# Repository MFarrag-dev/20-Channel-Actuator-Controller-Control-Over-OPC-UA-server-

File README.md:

# 20-Channel-Actuator-Controller-Control-Over-OPC-UA-server-
20 Channel Actuator Controller

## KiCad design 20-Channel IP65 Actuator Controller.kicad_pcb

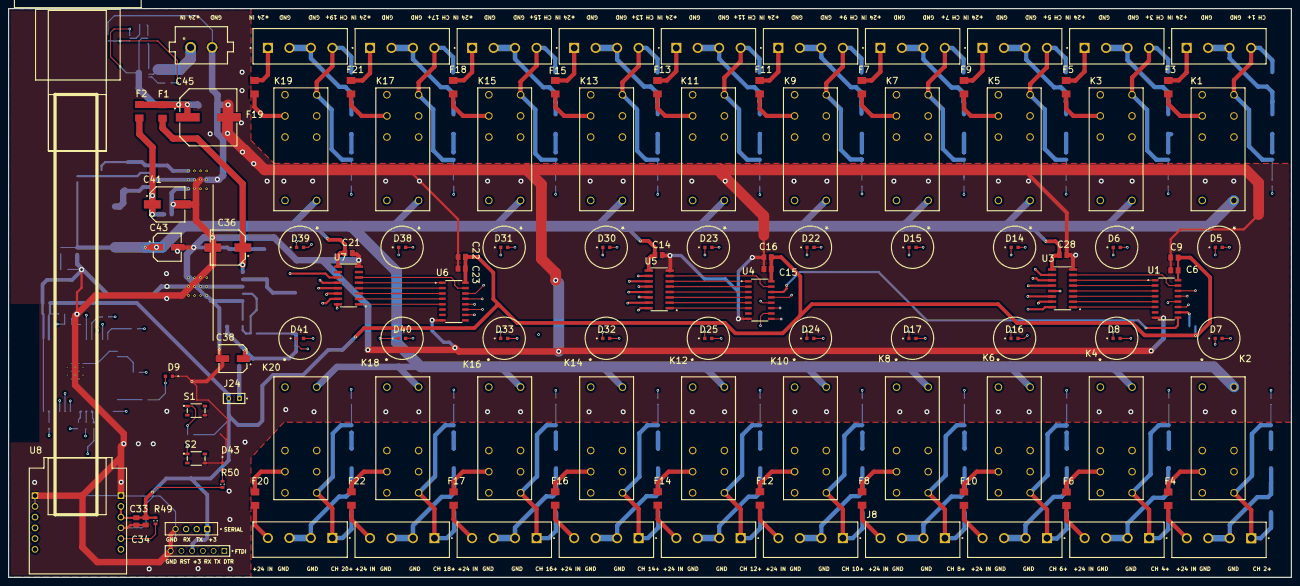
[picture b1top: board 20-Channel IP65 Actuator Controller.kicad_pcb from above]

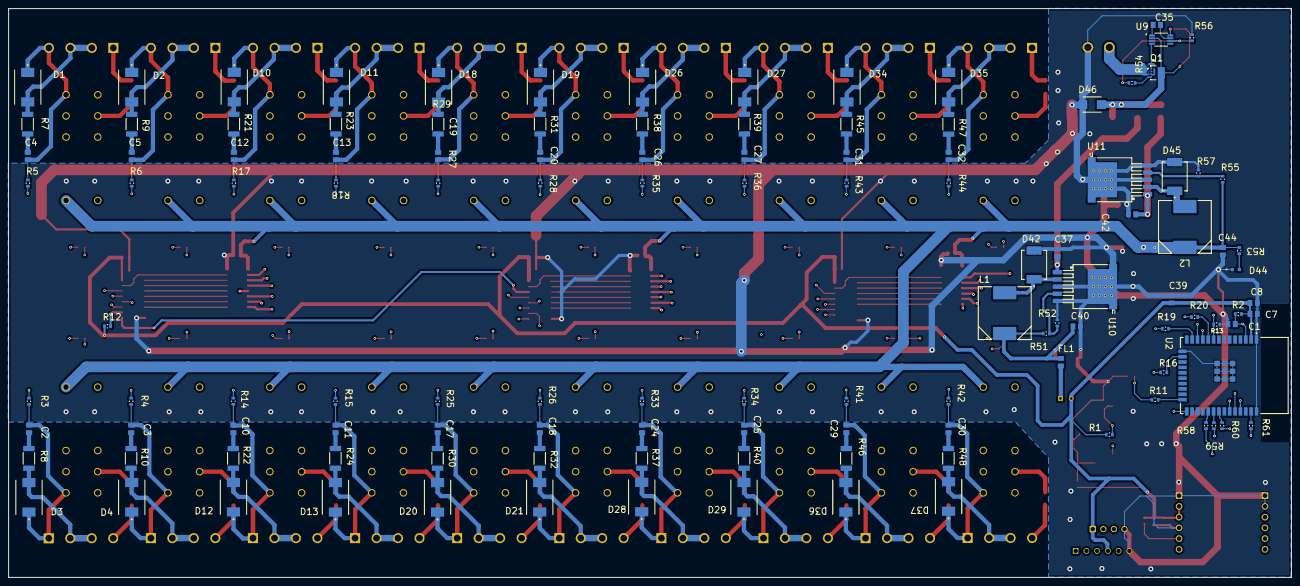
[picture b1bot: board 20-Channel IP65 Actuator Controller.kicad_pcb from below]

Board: 6 copper layers, 303.4 x 134.5 mm, 235 parts (120 on the bottom side), 205 nets.

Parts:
C1, C2, C3, C4, C5, C8, C9, C10, C11, C12, C13, C14, C16, C17, C18, C19, C20, C21, C23, C24, C25, C26, C27, C28, C29, C30, C31, C32, C34: 100nF; CAPC2012X88N
C6, C7, C15, C22, C33: 1uF; CAPC2012X88N
C35: 2.2uF; CAPC2012X88N
C36, C41: 100uF 50v; CAP_EEEHAH101UAP
C37, C42: 100nF 0805; CAPC2012X88N
C38, C43: 220uF 16v; CAP_EEEFTE221XAP
C39, C40, C44: 10uF 0805; CAPC2012X88N
C45: 470uF 50v; CAP_EEVTG1C471Q
D1, D2, D3, D4, D10, D11, D12, D13, D18, D19, D20, D21, D26, D27, D28, D29, D34, D35, D36, D37: SS54; SS54 DO-214AB SMC
D5, D6, D7, D8, D14, D15, D16, D17, D22, D23, D24, D25, D30, D31, D32, D33, D38, D39, D40, D41: Blue_LED; LED_0603
D9: LED_Green; LED_0603
D42, D45: SS34; DIO_SS34
D43: LED_Yellow; LED_0603
D44: LED_RED; LED_0603
D46: SMBJ28A; DIOM5436X244N
F1, F2: SF-1206SP550M-2; FUSC3115X66N
F3, F4, F5, F6, F7, F8, F9, F10, F11, F12, F13, F14, F15, F16, F17, F18, F19, F20, F21, F22: 0407002.WR; FUSC3115X66N
FL1: EMI Filter; BEADC2012X105N
J1, J2, J3, J4, J5, J6, J7, J8, J9, J10, J11, J12, J15, J16, J17, J18, J19, J20, J21, J22: 395316004; MOLEX_395316004
J13: HTSW-106-20-SM-S; SAMTEC_HTSW-106-20-SM-S
J14: B4B-XH-A(LF)(SN); JST_B4B-XH-A(LF)(SN)
J23: KF2EDGV-5.08-2P; 691305530002
J24: TD-101-X-A; SAMTEC_TD-101-X-A
K1, K2, K3, K4, K5, K6, K7, K8, K9, K10, K11, K12, K13, K14, K15, K16, K17, K18, K19, K20: G2RL-1-E DC5; RELAY_G2RL-1-E DC5_OMR
L1, L2: 33uH; INDM125125X600N
Q1: STL20N6F7; TRANS_STL3N65M2
R1, R2, R3, R4, R5, R6, R12, R13, R14, R15, R17, R18, R25, R26, R27, R28, R33, R34, R35, R36, R41, R42, R43, R44, R49: 10k; RES_ERJU03F1503V
R7, R8, R9, R10, R21, R22, R23, R24, R29, R30, R31, R32, R37, R38, R39, R40, R45, R46, R47, R48: 100R; RESC5025X65N
R11, R16, R19: 100R; RES_ERJU03F1503V
R20, R59, R60, R61: 22R; RES_ERJU03F1503V
R50: 470R; RES_ERJU03F1503V
R51: 3.2k; RES_ERJU03F1503V
R52, R57: 2k; RES_ERJU03F1503V
R53: 1k; RES_ERJU03F1503V
R54: 47R; RES_ERJU03F1503V
R55: 6.98k; RES_ERJU03F1503V
R56: 100k; RES_ERJU03F1503V
R58: 0R; RES_ERJU03F1503V
S1, S2: SKRPACE010; SW_SKRPACE010
U1, U4, U6: 74HC595D; SOP127P600X175-16N
U2: ESP32-WROOM-32; MODULE_ESP32-WROOM-32
U3, U5, U7: ULN2003AD; SOIC127P600X175-16N
U8: WIZ820IO; MODULE_WIZ820IO
U9: LM74610QDGKRQ1; SOP65P490X110-8N
U10, U11: LM2596S-ADJ/NOPB; KTT0005B

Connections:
+3.3: C6.1, C7.1, C8.1, C9.1, C15.1, C16.1, C22.1, C23.1, C33.1, C34.1, C39.2, J13.04, J14.1, J24.02, R1.2, R2.2, R12.1, R49.1, R50.2, U1.16, U2.2, U4.16, U6.16, U8.J2_2, U8.J2_3
+5.5: C14.1, C21.1, C28.1, C43.1, C44.1, K1.1, K2.8, K3.1, K4.8, K5.1, K6.8, K7.1, K8.8, K9.1, K10.8, K11.1, K12.8, K13.1, K14.8, K15.1, K16.8, K17.1, K18.8, K19.1, K20.8, L2.1, R53.2, R55.2, U3.9, U5.9, U7.9
+24: C45.1, D46.C, F1.1, F2.1, Q1.3, U9.2, U9.8
CH_1: K1.8, U3.10
CH_2: K2.1, U3.11
CH_3: K3.8, U3.12
CH_4: K4.1, U3.13
CH_5: K5.8, U3.14
CH_6: K6.1, U3.15
CH_7: K7.8, U3.16
CH_8: K8.1, U5.10
CH_9: K9.8, U5.11
CH_10: K10.1, U5.12
CH_11: K11.8, U5.13
CH_12: K12.1, U5.14
CH_13: K13.8, U5.15
CH_14: K14.1, U5.16
CH_15: K15.8, U7.16
CH_16: K16.1, U7.15
CH_17: K17.8, U7.14
CH_18: K18.1, U7.13
CH_19: K19.8, U7.12
CH_20: K20.1, U7.11
CLK: R19.1, U1.11, U4.11, U6.11
CLR: R12.2, U1.10, U2.11, U4.10, U6.10
DATA: R16.1, U1.14
DATA_2: U1.9, U4.14
DATA_3: U4.9, U6.14
DTR: J13.01, R1.1, S1.1, U2.25
EN: R13.2, U1.13, U2.9, U4.13, U6.13
FB_3.3: R51.1, R52.2, U10.4
FB_5.5: R55.1, R57.2, U11.4
GND: C1.1, C6.2, C7.2, C8.2, C9.2, C14.2, C15.2, C16.2, C21.2, C22.2, C23.2, C28.2, C33.2, C34.2, C36.2, C37.2, C38.2, C39.1, C40.2, C41.2, C42.2, C43.2, C44.2, C45.2, D9.2, D42.A, D43.2, D44.2, D45.A, D46.A, J13.06, J14.4, J23.2, R13.1, R52.1, R56.2, R57.1, S1.4, S2.4, U1.8, U2.1, U2.15, U2.38, U2.39, U3.8, U4.8, U5.8, U6.8, U7.8, U8.J1_1, U8.J1_2, U8.J2_1, U8.J2_4, U10.3, U10.5, U11.3, U11.5
Gate: R54.2, R56.1, U9.6
INT: U2.12, U8.J1_6
LATCH: R20.1, U1.12, U4.12, U6.12
NetC2_1: C2.1, R8.2
NetC2_2: C2.2, D3.C, J2.4, K2.5, R3.2
NetC3_1: C3.1, R10.2
NetC3_2: C3.2, D4.C, J4.4, K4.5, R4.2
NetC4_1: C4.1, R7.2
NetC4_2: C4.2, D1.C, J1.1, K1.4, R5.2
NetC5_1: C5.1, R9.2
NetC5_2: C5.2, D2.C, J3.1, K3.4, R6.2
NetC10_1: C10.1, R22.2
NetC10_2: C10.2, D12.C, J6.4, K6.5, R14.2
NetC11_1: C11.1, R24.2
NetC11_2: C11.2, D13.C, J8.4, K8.5, R15.2
NetC12_1: C12.1, R21.2
NetC12_2: C12.2, D10.C, J5.1, K5.4, R17.2
NetC13_1: C13.1, R23.2
NetC13_2: C13.2, D11.C, J7.1, K7.4, R18.2
NetC17_1: C17.1, R30.2
NetC17_2: C17.2, D20.C, J10.4, K10.5, R25.2
NetC18_1: C18.1, R32.2
NetC18_2: C18.2, D21.C, J12.4, K12.5, R26.2
NetC19_1: C19.1, R29.2
NetC19_2: C19.2, D18.C, J9.1, K9.4, R27.2
NetC20_1: C20.1, R31.2
NetC20_2: C20.2, D19.C, J11.1, K11.4, R28.2
NetC24_1: C24.1, R37.2
NetC24_2: C24.2, D28.C, J16.4, K14.5, R33.2
NetC25_1: C25.1, R40.2
NetC25_2: C25.2, D29.C, J18.4, K16.5, R34.2
NetC26_1: C26.1, R38.2
NetC26_2: C26.2, D26.C, J15.1, K13.4, R35.2
NetC27_1: C27.1, R39.2
NetC27_2: C27.2, D27.C, J17.1, K15.4, R36.2
NetC29_1: C29.1, R46.2
NetC29_2: C29.2, D36.C, J20.4, K18.5, R41.2
NetC30_1: C30.1, R48.2
NetC30_2: C30.2, D37.C, J22.4, K20.5, R42.2
NetC31_1: C31.1, R45.2
NetC31_2: C31.2, D34.C, J19.1, K17.4, R43.2
NetC32_1: C32.1, R47.2
NetC32_2: C32.2, D35.C, J21.1, K19.4, R44.2
NetC35_1: C35.1, U9.7
NetC35_2: C35.2, U9.1
NetC36_1: C36.1, C37.1, F1.2, U10.1
NetC38_1: C38.1, C40.1, FL1.1, L1.1, R51.2
NetC41_1: C41.1, C42.1, F2.2, U11.1
NetD1_A: D1.A, D5.2, J1.2, J1.3, R7.1
NetD2_A: D2.A, D6.2, J3.2, J3.3, R9.1
NetD3_A: D3.A, D7.2, J2.2, J2.3, R8.1
NetD4_A: D4.A, D8.2, J4.2, J4.3, R10.1
NetD5_1: D5.1, R5.1
NetD6_1: D6.1, R6.1
NetD7_1: D7.1, R3.1
NetD8_1: D8.1, R4.1
NetD9_1: D9.1, R11.1
NetD10_A: D10.A, D14.2, J5.2, J5.3, R21.1
NetD11_A: D11.A, D15.2, J7.2, J7.3, R23.1
NetD12_A: D12.A, D16.2, J6.2, J6.3, R22.1
NetD13_A: D13.A, D17.2, J8.2, J8.3, R24.1
NetD14_1: D14.1, R17.1
NetD15_1: D15.1, R18.1
NetD16_1: D16.1, R14.1
NetD17_1: D17.1, R15.1
NetD18_A: D18.A, D22.2, J9.2, J9.3, R29.1
NetD19_A: D19.A, D23.2, J11.2, J11.3, R31.1
NetD20_A: D20.A, D24.2, J10.2, J10.3, R30.1
NetD21_A: D21.A, D25.2, J12.2, J12.3, R32.1
NetD22_1: D22.1, R27.1
NetD23_1: D23.1, R28.1
NetD24_1: D24.1, R25.1
NetD25_1: D25.1, R26.1
NetD26_A: D26.A, D30.2, J15.2, J15.3, R38.1
NetD27_A: D27.A, D31.2, J17.2, J17.3, R39.1
NetD28_A: D28.A, D32.2, J16.2, J16.3, R37.1
NetD29_A: D29.A, D33.2, J18.2, J18.3, R40.1
NetD30_1: D30.1, R35.1
NetD31_1: D31.1, R36.1
NetD32_1: D32.1, R33.1
NetD33_1: D33.1, R34.1
NetD34_A: D34.A, D38.2, J19.2, J19.3, R45.1
NetD35_A: D35.A, D39.2, J21.2, J21.3, R47.1
NetD36_A: D36.A, D40.2, J20.2, J20.3, R46.1
NetD37_A: D37.A, D41.2, J22.2, J22.3, R48.1
NetD38_1: D38.1, R43.1
NetD39_1: D39.1, R44.1
NetD40_1: D40.1, R41.1
NetD41_1: D41.1, R42.1
NetD42_C: D42.C, L1.2, U10.2
NetD43_1: D43.1, R50.1
NetD44_1: D44.1, R53.1
NetD45_C: D45.C, L2.2, U11.2
NetF3_1: F3.1, J1.4
NetF3_2: F3.2, K1.6
NetF4_1: F4.1, J2.1
NetF4_2: F4.2, K2.3
NetF5_1: F5.1, J3.4
NetF5_2: F5.2, K3.6
NetF6_1: F6.1, J4.1
NetF6_2: F6.2, K4.3
NetF7_1: F7.1, J7.4
NetF7_2: F7.2, K7.6
NetF8_1: F8.1, J8.1
NetF8_2: F8.2, K8.3
NetF9_1: F9.1, J5.4
NetF9_2: F9.2, K5.6
NetF10_1: F10.1, J6.1
NetF10_2: F10.2, K6.3
NetF11_1: F11.1, J9.4
NetF11_2: F11.2, K9.6
NetF12_1: F12.1, J10.1
NetF12_2: F12.2, K10.3
NetF13_1: F13.1, J11.4
NetF13_2: F13.2, K11.6
NetF14_1: F14.1, J12.1
NetF14_2: F14.2, K12.3
NetF15_1: F15.1, J15.4
NetF15_2: F15.2, K13.6
NetF16_1: F16.1, J16.1
NetF16_2: F16.2, K14.3
NetF17_1: F17.1, J18.1
NetF17_2: F17.2, K16.3
NetF18_1: F18.1, J17.4
NetF18_2: F18.2, K15.6
NetF19_1: F19.1, J21.4
NetF19_2: F19.2, K19.6
NetF20_1: F20.1, J22.1
NetF20_2: F20.2, K20.3
NetF21_1: F21.1, J19.4
NetF21_2: F21.2, K17.6
NetF22_1: F22.1, J20.1
NetF22_2: F22.2, K18.3
NetFL1_2: FL1.2, J24.01
NetQ1_2: Q1.2, R54.1
NetR11_2: R11.2, U2.24
NetR16_2: R16.2, U2.16
NetR19_2: R19.2, U2.13
NetR20_2: R20.2, U2.10
NetR58_2: R58.2, U2.29
NetR59_2: R59.2, U2.30
NetR60_2: R60.2, U2.31
NetR61_2: R61.2, U2.37
RST: C1.2, J13.05, R2.1, S2.1, U2.3
RX: J13.03, J14.3, U2.34
SPI1: R59.1, U8.J1_4
SPI2: R60.1, U8.J2_6
SPI3: R58.1, U8.J1_5
SPI4: R61.1, U8.J1_3
Source: J23.1, Q1.1, U9.4
TCH_1: U1.15, U3.7
TCH_2: U1.1, U3.6
TCH_3: U1.2, U3.5
TCH_4: U1.3, U3.4
TCH_5: U1.4, U3.3
TCH_6: U1.5, U3.2
TCH_7: U1.6, U3.1
TCH_8: U4.15, U5.7
TCH_9: U4.1, U5.6
TCH_10: U4.2, U5.5
TCH_11: U4.3, U5.4
TCH_12: U4.4, U5.3
TCH_13: U4.5, U5.2
TCH_14: U4.6, U5.1
TCH_15: U6.15, U7.6
TCH_16: U6.1, U7.5
TCH_17: U6.2, U7.4
TCH_18: U6.3, U7.3
TCH_19: U6.4, U7.2
TCH_20: U6.5, U7.1
TX: J13.02, J14.2, U2.35
WIZ_RESET: R49.2, U2.33, U8.J2_5

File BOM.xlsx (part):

Quantity | Comment | Part NUM # | Package NUM # | Description | Designator | Footprint | LibRef | Link
31 | 100nF | C0805F104K5RACTU | 0805 | 0805 C 100nF Ceramic Multilayer Capacitor, 50 VDC, +125degC, X7R Dielec, +/-10%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 | C1, C2, C3, C4, C5, C8, C9, C10, C11, C12, C13, C14, C16, C17, C18, C19, C20, C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 | CAPC2012X88N | C0805F104K5RACTU | https://www.lcsc.com/product-detail/C2167849.html?s_z=n_C080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
5 | 1uF | CL21B105KBFNNNE | 0805 | 0805 C 100nF Ceramic Multilayer Capacitor, 50 VDC, +125degC, X7R Dielec, +/-10%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 | C6, C7, C15, C22, C33 | CAPC2012X88N | C0805F104K5RACTU | https://www.lcsc.com/product-detail/C28323.html?s_z=n_1uf
1 | 2.2uF 35v | CGA0805X7S225K350MT | 0805 | 0805 C 2.2uF Ceramic Multilayer Capacitor, 35 VDC, +125degC, X7R Dielec, +/-10%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 | C35 | CAPC2012X88N | C0805F104K5RACTU | https://www.lcsc.com/product-detail/C6119952.html?s_z=n_2.2u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
2 | 100uF 50v | RVT1H101M0810 | SMD 8x10.2mm | Capacitor,Alum Electrolytic,Cap 100 uF,Tol 20%,Vol-Rtg 50 VDC,SMT,8x10.2,TR | P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 | C36, C41 | CAP_EEEHAH101UAP | EEEHAH101UAP | https://www.lcsc.com/product-detail/C72480.html?s_z=s_Passiv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
2 | 220uF 16v | RVT1C221M0607 | SMD 6.3 x 7.7mm | 220ÂµF 16V Aluminum Electrolytic Capacitors Radial, Can - SMD 160 mohm @ 100kHz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 | C38, C43 | CAP_EEEFTE221XAP | EEEFTE221XAP | https://www.lcsc.com/product-detail/C72496.html?s_z=s_Passiv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
3 | 10uF | CL21A106KAYNNNE | 0805 | 0805 C 100nF Ceramic Multilayer Capacitor, 50 VDC, +125degC, X7R Dielec, +/-10%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 | C39, C40, C44 | CAPC2012X88N | C0805F104K5RACTU | https://www.lcsc.com/product-detail/C15850.html?s_z=n_10uf
1 | 470uF 50v | RVT1H471M1213 | SMD 12.5x13.5mm | Cap Aluminum 470uF 16V 20% (12.5 X 13.5mm) SMD 0.12 Ohm 800mA 2000h 125Â°C T/R | C45 | CAP_EEVTG1C471Q | EEVTG1C471Q | https://www.lcsc.com/product-detail/C90272.html?s_z=s_Passiv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
20 | SS54 | SS54 | SMC(DO-214AB) | Diode Schottky 40 V 5A Surface Mount DO-214AB (SMC) | D1, D2, D3, D4, D10, D11, D12, D13, D18, D19, D20, D21, D26, D27, D28, D29, D34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 | SS54 DO-214AB SMC | SS54 DO-214AB SMC | https://www.lcsc.com/product-detail/C211777.html?s_z=n_SS54%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
20 | Blue_LED | A-SP192DGHC-C01-4T | 0603 | LED; SMD; 0603; Blue; 50-150mcd; 1.6x0.8mm; 120Â°; 20mA; | D5, D6, D7, D8, D14, D15, D16, D17, D22, D23, D24, D25, D30, D31, D32, D33, D38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 | LED_0603 | LED | https://www.lcsc.com/product-detail/C125103.html?s_z=n_led%2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
1 | LED_Green | A-SP192DGHC-C01-4T | 0603 | LED; SMD; 0603; Blue; 50-150mcd; 1.6x0.8mm; 120Â°; 20mA; | D9 | LED_0603 | LED | https://www.lcsc.com/product-detail/C19171301.html?s_z=n_led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
2 | SS34 | SS34 | SMC(DO-214AB) | 3A, 40V, Schottky Rectifier | D42, D45 | DIO_SS34 | SS34 | https://www.lcsc.com/product-detail/C154551.html?s_z=n_ss34
1 | LED_Yellow | SZYY0603Y | 0603 | LED; SMD; 0603; Blue; 50-150mcd; 1.6x0.8mm; 120Â°; 20mA; | D43 | LED_0603 | LED | https://www.lcsc.com/product-detail/C434424.html?s_z=n_led%2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
1 | LED_RED | MHT192CRCT | 0603 | LED; SMD; 0603; Blue; 50-150mcd; 1.6x0.8mm; 120Â°; 20mA; | D44 | LED_0603 | LED | https://www.lcsc.com/product-detail/C389517.html?s_z=n_led%2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
1 | SMBJ28A | SMBJ28A | DO-214AA | TVS Diode, 600W, 28V, -65 to 150 Operating Temp, Surface Mount, SMBJ Series | L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 | D46 | DIOM5436X244N | SMBJ28A | https://www.lcsc.com/product-detail/C178227.html?s_z=n_smbj28a
2 | Fuse 1A | SF-1206SP050-2 | 1206 | Slow Blow Fuse 1A | F1, F2 | FUSC3115X66N | SF-1206SP550M-2 | https://www.lcsc.com/product-detail/C1972689.html?s_z=n_SF-1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
20 | Fuse 2A | 0407002.WR | 1206 | Slow Blow Fuse 2A | F3, F4, F5, F6, F7, F8, F9, F10, F11, F12, F13, F14, F15, F16, F17, F18, F19, F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 | FUSC3115X66N | SF-1206SP550M-2 | https://www.lcsc.com/product-detail/C1882499.html?s_z=n_0407002.WR
1 | EMI Filter | BLM21PG221SN1D | 0805 | Ferrite Beads 220Ω@100MHz 2A | FL1 | BEADC2012X105N | BLM21SP111SH1D | https://www.lcsc.com/product-detail/C85840.html?s_z=n_BLM21P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
20 | Terminal Block 4P | KF2EDGV-5.08-4P | 4P 5.08MM | 4 Position Terminal Block Header, Male Pins, Shrouded (4 Side) 0.200 (5.08mm) V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 | J1, J2, J3, J4, J5, J6, J7, J8, J9, J10, J11, J12, J15, J16, J17, J18, J19, J20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 | MOLEX_395316004 | 395316004 | https://makerselectronics.com/product/terminal-block-kf2edgv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
1 | Pads Only | - | - | 'FTDI NO Soldering | J13 | SAMTEC_HTSW-106-20-SM-S | HTSW-106-20-SM-S
1 | Pads Only | - | - | Serial No Soldering | J14 | JST_B4B-XH-A(LF)(SN) | B4B-XH-A(LF)(SN)
1 | KF2EDGV-5.08-2P | KF2EDGV-5.08-2P | 2P 5.08MM | 2 Position Terminal Block Header, Male Pins, Shrouded (4 Side) 0.200" (5.08mm) 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 | J23 | 691305530002 | 691305530002 | https://makerselectronics.com/product/terminal-block-kf2edgv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
1 | 2P Header |  |  | 2 Position Header Connector Male Pin Gold | J24 | SAMTEC_TD-101-X-A | TD-101-X-A | https://lampatronics.com/product/single-male-pin-header-stra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
1 | Jumper Shunt 2 Pin |  |  | Jumper | J24 |  |  | https://makerselectronics.com/product/jumper-shunt-2-pin-2-5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
20 | Relay Base | G2R/G2RL Base | DIP,28.8x12.5mm | PCB Relay Socket 8Pins (G2R/G2RL) |  |  |  | https://www.ebay.com/itm/365465078493?chn=ps&_trkparms=ispr%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
20 | G2RL-1-E DC5 | G2RL-1-E DC5 | DIP,28.8x12.5mm | G2RL-1-E-DC5 Two Pole | K1, K2, K3, K4, K5, K6, K7, K8, K9, K10, K11, K12, K13, K14, K15, K16, K17, K18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 | RELAY_G2RL-1-E DC5_OMR | G2RL-1-E DC5 | https://eu.mouser.com/ProductDetail/Omron-Electronics/G2RL-1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
2 | 33uH | DR125-330-R | SMD 12.5x12.5mm | Inductor, Wirewound, Shielded, 33uH, 50.5mOhm, 3.28A, Surface Mount, DR Series 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 | L1, L2 | INDM125125X600N | DR125-330-R | https://www.lcsc.com/product-detail/C2453822.html?s_z=n_DR125-330-R
1 | STL20N6F7 | STL20N6F7 | VDFN-8-Power | MOSFET, N, 60V | Q1 | TRANS_STL3N65M2 | STL20N6F7 | https://www.lcsc.com/product-detail/C2969815.html?s_z=n_STL20N6F7
25 | 10k | RC0603FR-0710KL | 0603 | Fixed Resistor CRGCQ 1206 10K 5% | R1, R2, R3, R4, R5, R6, R12, R13, R14, R15, R17, R18, R25, R26, R27, R28, R33, 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 | RES_ERJU03F1503V | Resistor 0603 | https://www.lcsc.com/product-detail/C98220.html?s_z=n_10k%25200603
20 | 100R | FRC2010J101 TS | 2010 | Fixed Resistor CRGCQ 201010K 5% | R7, R8, R9, R10, R21, R22, R23, R24, R29, R30, R31, R32, R37, R38, R39, R40, R4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 | RESC5025X65N | Resistor 2010 | https://www.lcsc.com/product-detail/C2907558.html?s_z=n_100%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
3 | 100R | RC0603FR-07100RL | 0603 | Fixed Resistor CRGCQ 1206 10K 5% | R11, R16, R19 | RES_ERJU03F1503V | Resistor 0603 | https://www.lcsc.com/product-detail/C105588.html?s_z=n_100oh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
4 | 22R | 0603WAF220JT5E | 0603 | Fixed Resistor CRGCQ 1206 10K 5% | R20, R59, R60, R61 | RES_ERJU03F1503V | Resistor 0603 | https://www.lcsc.com/product-detail/C23345.html?s_z=n_22R%25200603
1 | 470R | RC0603FR-07470RL | 0603 | Fixed Resistor CRGCQ 1206 10K 5% | R50 | RES_ERJU03F1503V | Resistor 0603 | https://www.lcsc.com/product-detail/C114669.html?s_z=n_470R%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
1 | 3.2k | RT0603BRD073K2L | 0603 | Fixed Resistor CRGCQ 1206 10K 5% | R51 | RES_ERJU03F1503V | Resistor 0603 | https://www.lcsc.com/product-detail/C861375.html?s_z=n_3.2k%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
2 | 2k | 0603WAF2001T5E | 0603 | Fixed Resistor CRGCQ 1206 10K 5% | R52, R57 | RES_ERJU03F1503V | Resistor 0603 | https://www.lcsc.com/product-detail/C22975.html?s_z=n_2k%25200603
1 | 1k | RC0603FR-071KL | 0603 | Fixed Resistor CRGCQ 1206 10K 5% | R53 | RES_ERJU03F1503V | Resistor 0603 | https://www.lcsc.com/product-detail/C22548.html?s_z=n_1k%25200603
1 | 47R | FRC0603J470 TS | 0603 | Fixed Resistor CRGCQ 1206 10K 5% | R54 | RES_ERJU03F1503V | Resistor 0603 | https://www.lcsc.com/product-detail/C2907174.html?s_z=n_47R%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
1 | 6.98k | RT0603BRD076K98L | 0603 | Fixed Resistor CRGCQ 1206 10K 5% | R55 | RES_ERJU03F1503V | Resistor 0603 | https://www.lcsc.com/product-detail/C861540.html?s_z=n_6.98k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
1 | 100k | RC0603FR-07100KL | 0603 | Fixed Resistor CRGCQ 1206 10K 5% | R56 | RES_ERJU03F1503V | Resistor 0603 | https://www.lcsc.com/product-detail/C14675.html?s_z=n_100k%25200603
1 | 0R | RC0603JR-070RL | 0603 | Fixed Resistor CRGCQ 1206 10K 5% | R58 | RES_ERJU03F1503V | Resistor 0603 | https://www.lcsc.com/product-detail/C95177.html?s_z=n_0R%25200603
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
